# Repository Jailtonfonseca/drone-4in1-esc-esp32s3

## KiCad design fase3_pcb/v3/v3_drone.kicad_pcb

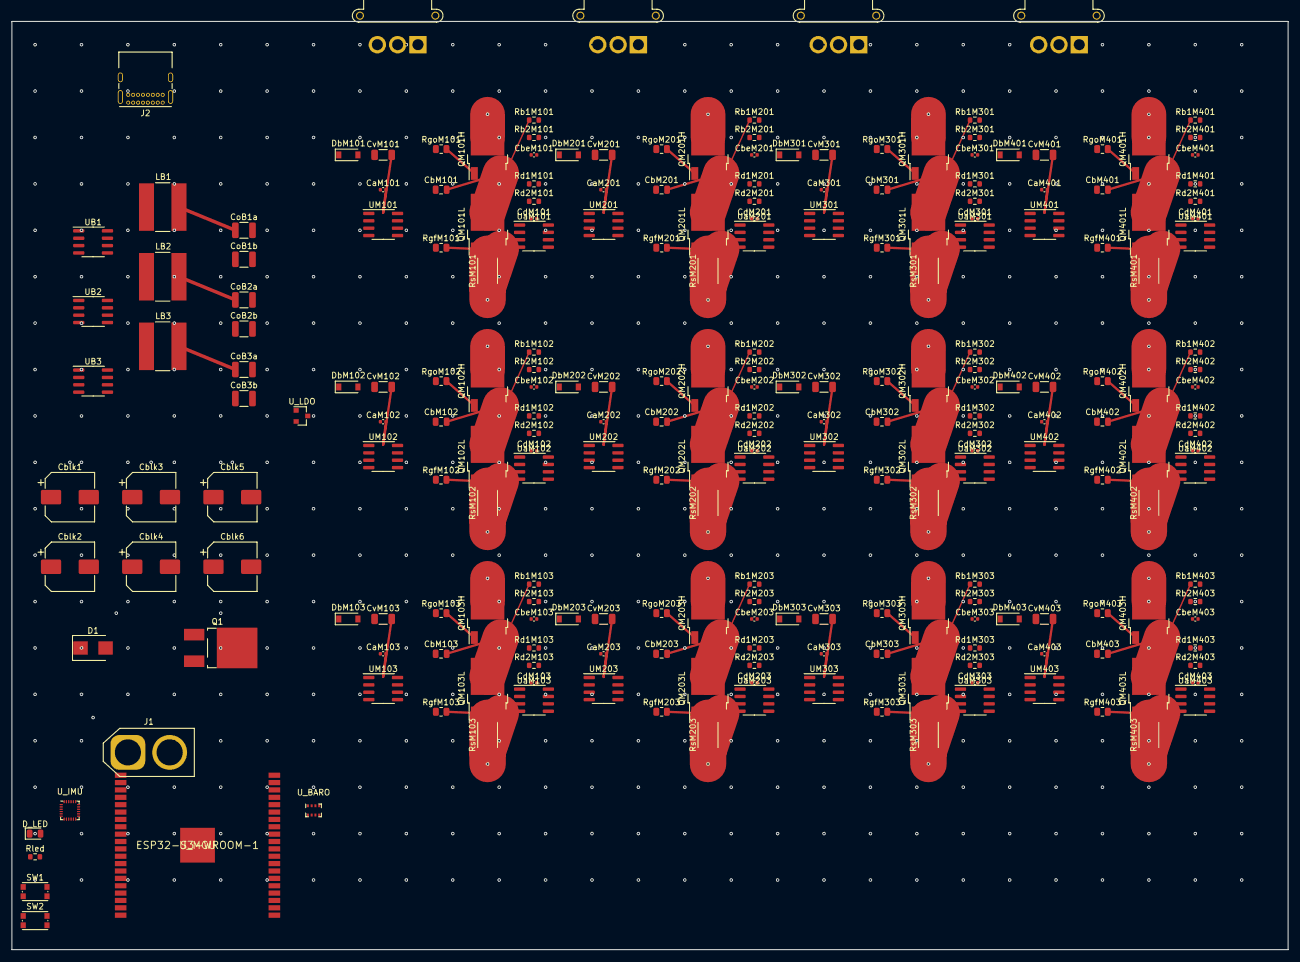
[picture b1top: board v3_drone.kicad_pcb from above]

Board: 4 copper layers, 220.0 x 160.0 mm, 238 parts (0 on the bottom side), 68 nets.

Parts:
CaM101, CaM102, CaM103, CaM201, CaM202, CaM203, CaM301, CaM302, CaM303, CaM401, CaM402, CaM403: C_0402_1005Metric
CbM101, CbM102, CbM103, CbM201, CbM202, CbM203, CbM301, CbM302, CbM303, CbM401, CbM402, CbM403: C_0805_2012Metric
CbeM101, CbeM102, CbeM103, CbeM201, CbeM202, CbeM203, CbeM301, CbeM302, CbeM303, CbeM401, CbeM402, CbeM403: C_0402_1005Metric
Cblk1, Cblk2, Cblk3, Cblk4, Cblk5, Cblk6: CP_Elec_8x10
CdM101, CdM102, CdM103, CdM201, CdM202, CdM203, CdM301, CdM302, CdM303, CdM401, CdM402, CdM403: C_0402_1005Metric
CoB1a, CoB1b, CoB2a, CoB2b, CoB3a, CoB3b: C_1210_3225Metric
CvM101, CvM102, CvM103, CvM201, CvM202, CvM203, CvM301, CvM302, CvM303, CvM401, CvM402, CvM403: C_1206_3216Metric
D1: D_SMB
D_LED: LED_0805_2012Metric
DbM101, DbM102, DbM103, DbM201, DbM202, DbM203, DbM301, DbM302, DbM303, DbM401, DbM402, DbM403: D_SOD-123
J1: AMASS_XT60-F_1x02_P7.20mm_Vertical
J2: USB_C_Receptacle_GCT_USB4085
J_M1, J_M2, J_M3, J_M4: AMASS_MR30PW-FB_1x03_P3.50mm_Horizontal
LB1, LB2, LB3: L_Bourns-SRN8040_8x8.15mm
Q1: TO-252-2_TabPin1
QM101H, QM101L, QM102H, QM102L, QM103H, QM103L, QM201H, QM201L, QM202H, QM202L, QM203H, QM203L, QM301H, QM301L, QM302H, QM302L, QM303H, QM303L, QM401H, QM401L, QM402H, QM402L, QM403H, QM403L: TO-252-3_TabPin2
Rb1M101, Rb1M102, Rb1M103, Rb1M201, Rb1M202, Rb1M203, Rb1M301, Rb1M302, Rb1M303, Rb1M401, Rb1M402, Rb1M403, Rb2M101, Rb2M102, Rb2M103, Rb2M201, Rb2M202, Rb2M203, Rb2M301, Rb2M302, Rb2M303, Rb2M401, Rb2M402, Rb2M403: R_0603_1608Metric
Rd1M101, Rd1M102, Rd1M103, Rd1M201, Rd1M202, Rd1M203, Rd1M301, Rd1M302, Rd1M303, Rd1M401, Rd1M402, Rd1M403, Rd2M101, Rd2M102, Rd2M103, Rd2M201, Rd2M202, Rd2M203, Rd2M301, Rd2M302, Rd2M303, Rd2M401, Rd2M402, Rd2M403: R_0603_1608Metric
RgfM101, RgfM102, RgfM103, RgfM201, RgfM202, RgfM203, RgfM301, RgfM302, RgfM303, RgfM401, RgfM402, RgfM403: R_0805_2012Metric
RgoM101, RgoM102, RgoM103, RgoM201, RgoM202, RgoM203, RgoM301, RgoM302, RgoM303, RgoM401, RgoM402, RgoM403: R_0805_2012Metric
Rled: R_0603_1608Metric
RsM101, RsM102, RsM103, RsM201, RsM202, RsM203, RsM301, RsM302, RsM303, RsM401, RsM402, RsM403: R_2512_6332Metric
SW1, SW2: SW_Push_1P1T_NO_CK_KMR2
UB1, UB2, UB3: SOIC-8_3.9x4.9mm_P1.27mm
UM101, UM102, UM103, UM201, UM202, UM203, UM301, UM302, UM303, UM401, UM402, UM403: SOIC-8_3.9x4.9mm_P1.27mm
U_BARO: Bosch_LGA-8_2x2.5mm_P0.65mm_ClockwisePinNumbering
U_IMU: InvenSense_QFN-24_3x3mm_P0.4mm
U_LDO: SOT-23
U_MCU: ESP32-S3-WROOM-1
UaM101, UaM102, UaM103, UaM201, UaM202, UaM203, UaM301, UaM302, UaM303, UaM401, UaM402, UaM403: SOIC-8_3.9x4.9mm_P1.27mm

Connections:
3V3: CoB3a.1, CoB3b.1, D_LED.2, LB3.2, U_LDO.3
5V: CoB2a.1, CoB2b.1, LB2.2
12V: CoB1a.1, CoB1b.1, CvM101.1, CvM102.1, CvM103.1, CvM201.1, CvM202.1, CvM203.1, CvM301.1, CvM302.1, CvM303.1, CvM401.1, CvM402.1, CvM403.1, DbM101.1, DbM102.1, DbM103.1, DbM201.1, DbM202.1, DbM203.1, DbM301.1, DbM302.1, DbM303.1, DbM401.1, DbM402.1, DbM403.1, LB1.2
GHM101: QM101H.1, RgoM101.2
GHM102: QM102H.1, RgoM102.2
GHM103: QM103H.1, RgoM103.2
GHM201: QM201H.1, RgoM201.2
GHM202: QM202H.1, RgoM202.2
GHM203: QM203H.1, RgoM203.2
GHM301: QM301H.1, RgoM301.2
GHM302: QM302H.1, RgoM302.2
GHM303: QM303H.1, RgoM303.2
GHM401: QM401H.1, RgoM401.2
GHM402: QM402H.1, RgoM402.2
GHM403: QM403H.1, RgoM403.2
GLM101: QM101L.1, RgfM101.2
GLM102: QM102L.1, RgfM102.2
GLM103: QM103L.1, RgfM103.2
GLM201: QM201L.1, RgfM201.2
GLM202: QM202L.1, RgfM202.2
GLM203: QM203L.1, RgfM203.2
GLM301: QM301L.1, RgfM301.2
GLM302: QM302L.1, RgfM302.2
GLM303: QM303L.1, RgfM303.2
GLM401: QM401L.1, RgfM401.2
GLM402: QM402L.1, RgfM402.2
GLM403: QM403L.1, RgfM403.2
GND: CaM101.2, CaM102.2, CaM103.2, CaM201.2, CaM202.2, CaM203.2, CaM301.2, CaM302.2, CaM303.2, CaM401.2, CaM402.2, CaM403.2, CbeM101.2, CbeM102.2, CbeM103.2, CbeM201.2, CbeM202.2, CbeM203.2, CbeM301.2, CbeM302.2, CbeM303.2, CbeM401.2, CbeM402.2, CbeM403.2, Cblk1.2, Cblk2.2, Cblk3.2, Cblk4.2, Cblk5.2, Cblk6.2, CdM101.2, CdM102.2, CdM103.2, CdM201.2, CdM202.2, CdM203.2, CdM301.2, CdM302.2, CdM303.2, CdM401.2, CdM402.2, CdM403.2, CoB1a.2, CoB1b.2, CoB2a.2, CoB2b.2, CoB3a.2, CoB3b.2, CvM101.2, CvM102.2, CvM103.2, CvM201.2, CvM202.2, CvM203.2, CvM301.2, CvM302.2, CvM303.2, CvM401.2, CvM402.2, CvM403.2, D1.2, J1.2, Rb2M101.2, Rb2M102.2, Rb2M103.2, Rb2M201.2, Rb2M202.2, Rb2M203.2, Rb2M301.2, Rb2M302.2, Rb2M303.2, Rb2M401.2, Rb2M402.2, Rb2M403.2, Rd1M101.2, Rd1M102.2, Rd1M103.2, Rd1M201.2, Rd1M202.2, Rd1M203.2, Rd1M301.2, Rd1M302.2, Rd1M303.2, Rd1M401.2, Rd1M402.2, Rd1M403.2, Rd2M101.2, Rd2M102.2, Rd2M103.2, Rd2M201.2, Rd2M202.2, Rd2M203.2, Rd2M301.2, Rd2M302.2, Rd2M303.2, Rd2M401.2, Rd2M402.2, Rd2M403.2, Rled.2, RsM101.2, RsM102.2, RsM103.2, RsM201.2, RsM202.2, RsM203.2, RsM301.2, RsM302.2, RsM303.2, RsM401.2, RsM402.2, RsM403.2, U_LDO.2
LED_K: D_LED.1, Rled.1
PHM101: CbM101.2, QM101H.3, QM101L.2, Rb1M101.1
PHM102: CbM102.2, QM102H.3, QM102L.2, Rb1M102.1
PHM103: CbM103.2, QM103H.3, QM103L.2, Rb1M103.1
PHM201: CbM201.2, QM201H.3, QM201L.2, Rb1M201.1
PHM202: CbM202.2, QM202H.3, QM202L.2, Rb1M202.1
PHM203: CbM203.2, QM203H.3, QM203L.2, Rb1M203.1
PHM301: CbM301.2, QM301H.3, QM301L.2, Rb1M301.1
PHM302: CbM302.2, QM302H.3, QM302L.2, Rb1M302.1
PHM303: CbM303.2, QM303H.3, QM303L.2, Rb1M303.1
PHM401: CbM401.2, QM401H.3, QM401L.2, Rb1M401.1
PHM402: CbM402.2, QM402H.3, QM402L.2, Rb1M402.1
PHM403: CbM403.2, QM403H.3, QM403L.2, Rb1M403.1
SNM101: QM101L.3, RsM101.1
SNM102: QM102L.3, RsM102.1
SNM103: QM103L.3, RsM103.1
SNM201: QM201L.3, RsM201.1
SNM202: QM202L.3, RsM202.1
SNM203: QM203L.3, RsM203.1
SNM301: QM301L.3, RsM301.1
SNM302: QM302L.3, RsM302.1
SNM303: QM303L.3, RsM303.1
SNM401: QM401L.3, RsM401.1
SNM402: QM402L.3, RsM402.1
SNM403: QM403L.3, RsM403.1
VBAT: J1.1, Q1.1
VBAT_PROT: CaM101.1, CaM102.1, CaM103.1, CaM201.1, CaM202.1, CaM203.1, CaM301.1, CaM302.1, CaM303.1, CaM401.1, CaM402.1, CaM403.1, Cblk1.1, Cblk2.1, Cblk3.1, Cblk4.1, Cblk5.1, Cblk6.1, D1.1, Q1.2, QM101H.2, QM102H.2, QM103H.2, QM201H.2, QM202H.2, QM203H.2, QM301H.2, QM302H.2, QM303H.2, QM401H.2, QM402H.2, QM403H.2
VBM101: CbM101.1, DbM101.2
VBM102: CbM102.1, DbM102.2
VBM103: CbM103.1, DbM103.2
VBM201: CbM201.1, DbM201.2
VBM202: CbM202.1, DbM202.2
VBM203: CbM203.1, DbM203.2
VBM301: CbM301.1, DbM301.2
VBM302: CbM302.1, DbM302.2
VBM303: CbM303.1, DbM303.2
VBM401: CbM401.1, DbM401.2
VBM402: CbM402.1, DbM402.2
VBM403: CbM403.1, DbM403.2
VREF: CdM101.1, CdM102.1, CdM103.1, CdM201.1, CdM202.1, CdM203.1, CdM301.1, CdM302.1, CdM303.1, CdM401.1, CdM402.1, CdM403.1, Rd1M101.1, Rd1M102.1, Rd1M103.1, Rd1M201.1, Rd1M202.1, Rd1M203.1, Rd1M301.1, Rd1M302.1, Rd1M303.1, Rd1M401.1, Rd1M402.1, Rd1M403.1, Rd2M101.1, Rd2M102.1, Rd2M103.1, Rd2M201.1, Rd2M202.1, Rd2M203.1, Rd2M301.1, Rd2M302.1, Rd2M303.1, Rd2M401.1, Rd2M402.1, Rd2M403.1
